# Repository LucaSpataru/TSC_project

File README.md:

# TSC_project
Pentru acest proiect am avut de implementat PCBul unui ebook reader si asamblarea acestuia in carcasa alaturi de o baterie si display.
Primul pas al proiectului a fost creearea schemei electrice ce consta in plasarea si conectarea componentelor.
Componenta principala este microcontrollerul ESP32-C6 care gestioneaza și coordoneaza functionarea celorlalte componente.
# Pini folositi
| Componentă                            | Pini ESP C6                         | Funcție                                                       |
|--------------------------------------|-------------------------------------|---------------------------------------------------------------|
| SAMACSYS_PARTS_USB4110-GF-AUSB4      | 13 (USB_D-), 14 (USB_D+)            | Încărcare baterie via USB                                     |
| QWIIC_RIGHT_ANGLE + BME680           | 19 (SDA), 20 (SCL)                  | Măsurare temperatură, calitate aer, umiditate (energy mgmt)  |
| 112A-TAAR-R03_ATTEND (SD card port)  | 4 (SS_SD), 6 (SCK), 7 (MOSI), 27 (MISO) | Transfer de date (card SD)                                 |
| FH34SRJ-24S-0.5SH_99_ (Display header)| 7 (MOSI), 6 (SCK), 11 (EPD_CS), 5 (EPD_DC), 21 (EPD_RST), 26 (EPD_BUSY) | Conectare display          |
| W25Q512JVEIQ (64MB Flash extern)     | 6 (SCK), 7 (MOSI), 27 (MISO), 12 (FLASH_CS) | Stocare de date                                       |
| Butoane (CHANGE, RESET, BOOT)        | 23 (IO/CHANGE), 3 (RESET), 15 (IO/BOOT) | Interfață utilizator (comenzi)                          |
| DS3231SN# (RTC module)               | 8 (INT_RTC), 19 (SDA), 20 (SCL), 9 (32KHZ), 16 (RTC_RST) | Ceas în timp real                              |

De asemenea sunt implementate test paduri, un regulator de tensiune si linii de protectie pentru a putea asigura functionarea corecta a dispozitivului.

Urmatoarul pas a constat in aranjarea componentelor pe placa, decuparea acesteia pentru a se potrivi in carcasa si pentru a nu incurca alte componente precum microcontrollerul si butoanele,
rutarea semnalelor si desenarea planului de masa pe fata si pe spate.
Am intampinat unele probleme precum marimea padurilor pentru componenta MAX17048G+T10 care nu se potriveau cu regulile de rutare, si marimea padurilor bobinei care erau prea mici - am modificat footprintul componentelor.
Am dat approve la 2 erori comune de tip Board Outline Clearance pentru mufa USB4.
Am plasat componentele cat mai eficient, si de asemenea am aranjat ca numele componentelor sa fie vizibile pe silkscreen.

Mai departe am cautat pentru fiecare componenta folosita modele 3D unde am comparat footprinturile pieselor gasite pentru a alege modelul corespunzator.

Ultimul pas a constat in partea 3D unde am plasat placa in carcasa, aici am facut o modificare ce se poate observa in imaginile buttons_mod, deoarece felul in care am pus butoanele se intersectau cu o bucata de plastic
care am micsorat-o. Butoanele ar trebuii sa functioneze fara probleme acum.
Dupa ce m-am asigurat ca mufele sunt aliniate cu componentele ce ies de pe placa, am creeat un model de baterie si unul de display si le-am aranjat si pe acestea in interiorul dispozitivului.

In cele din urma am generat fisierele BOM, PNP si gerbers care se afla in fisierul Manufacturing.
De asemenea am realizat o animatie cu exploded view, dar si un fisier .step cum este specificat in cerinta.
# BOM
| Componentă                     | Link de cumpărare |
|----------------------------|-------------------|
| ADAFRUIT_LEDCHIP-LED0603   | [Mouser](https://ro.mouser.com/ProductDetail/ams-OSRAM/KW-EELP41.RU-S1U1-3K6L-3X4X-5-R18?qs=sGAEpiMZZMt82OzCyDsLFIOEctO0UgBCyNaG5LP3KGg%3D)                 |
| SJ                         | [Mouser](https://ro.mouser.com/ProductDetail/Chip-Quik/WWSWLT.040-200g?qs=i8QVZAFTkqRTFq30mTreAQ%3D%3D)                 |
| CPH3225A (Supercapacitor)  | [Mouser](https://ro.mouser.com/ProductDetail/Seiko-Semiconductors/CPH3225A?qs=3etwrb1wR%252BhUOph6lAO7eg%3D%3D) |
| DS3231SN# (RTC)           | [SnapEDA](https://www.snapeda.com/parts/DS3231SN%23/Analog+Devices/view-part/?ref=eda) |
| ESP32-C6-WROOM-1-N8       | [SnapEDA](https://www.snapeda.com/parts/ESP32-C6-WROOM-1-N8/Espressif+Systems/view-part/?ref=eda) |
| FH34SRJ-24S-0.5SH_99_     | [Mouser](https://www.mouser.co.uk/ProductDetail/Hirose-Connector/FH34SRJ-24S-0.5SH99?qs=vcbW%252B4%252BSTIpKBl5ap9J8Fw%3D%3D) |
| MAX17048G+T10 (Fuel Gauge)| [SnapEDA](https://www.snapeda.com/parts/MAX17048G+T10/Analog+Devices/view-part/?ref=eda) |
| MBR0530 (Schottky Diode)  | [SnapEDA](https://www.snapeda.com/parts/MBR0530/Onsemi/view-part/?ref=eda) |
| PGB1010603MR (TVS Diode)  | [SnapEDA](https://www.snapeda.com/parts/PGB1010603MR/Littelfuse/view-part/?ref=eda) |
| SI1308EDL-T1-GE3 (MOSFET) | [SnapEDA](https://www.snapeda.com/parts/SI1308EDL-T1-GE3/Vishay+Siliconix/view-part/?ref=eda) |
| USBLC6-2SC6Y (ESD Protection)| [SnapEDA](https://www.snapeda.com/parts/USBLC6-2SC6Y/STMicroelectronics/view-part/?ref=eda) |
| W25Q512JVEIQ (Flash Memory)| [SnapEDA](https://www.snapeda.com/parts/W25Q512JVEIQ/Winbond+Electronics/view-part/?ref=eda) |
| XC6220A331MR-G (LDO Regulator)| [Mouser](https://www.mouser.co.uk/ProductDetail/Torex-Semiconductor/XC6220A331MR-G?qs=AsjdqWjXhJ8ZSWznL1J0gg%3D%3D) |
| BD5229G-TR (Voltage Detector)| [Mouser](https://www.mouser.co.uk/ProductDetail/ROHM-Semiconductor/BD5229G-TR?qs=4kLU8WoGk0vvnhrrYwdszw%3D%3D) |
| BME680 (Environmental Sensor)| [Mouser](https://ro.mouser.com/ProductDetail/Bosch-Sensortec/BME680?qs=v271MhAjFHjo0yA%2FC4OnDQ%3D%3D)                 |
| 112A-TAAR-R03_ATTEND (SD Card Socket)| [DigiKey](https://www.digikey.ro/en/products/detail/attend-technology/112A-TAAR-R03/17633923)                 |

# Diagrama

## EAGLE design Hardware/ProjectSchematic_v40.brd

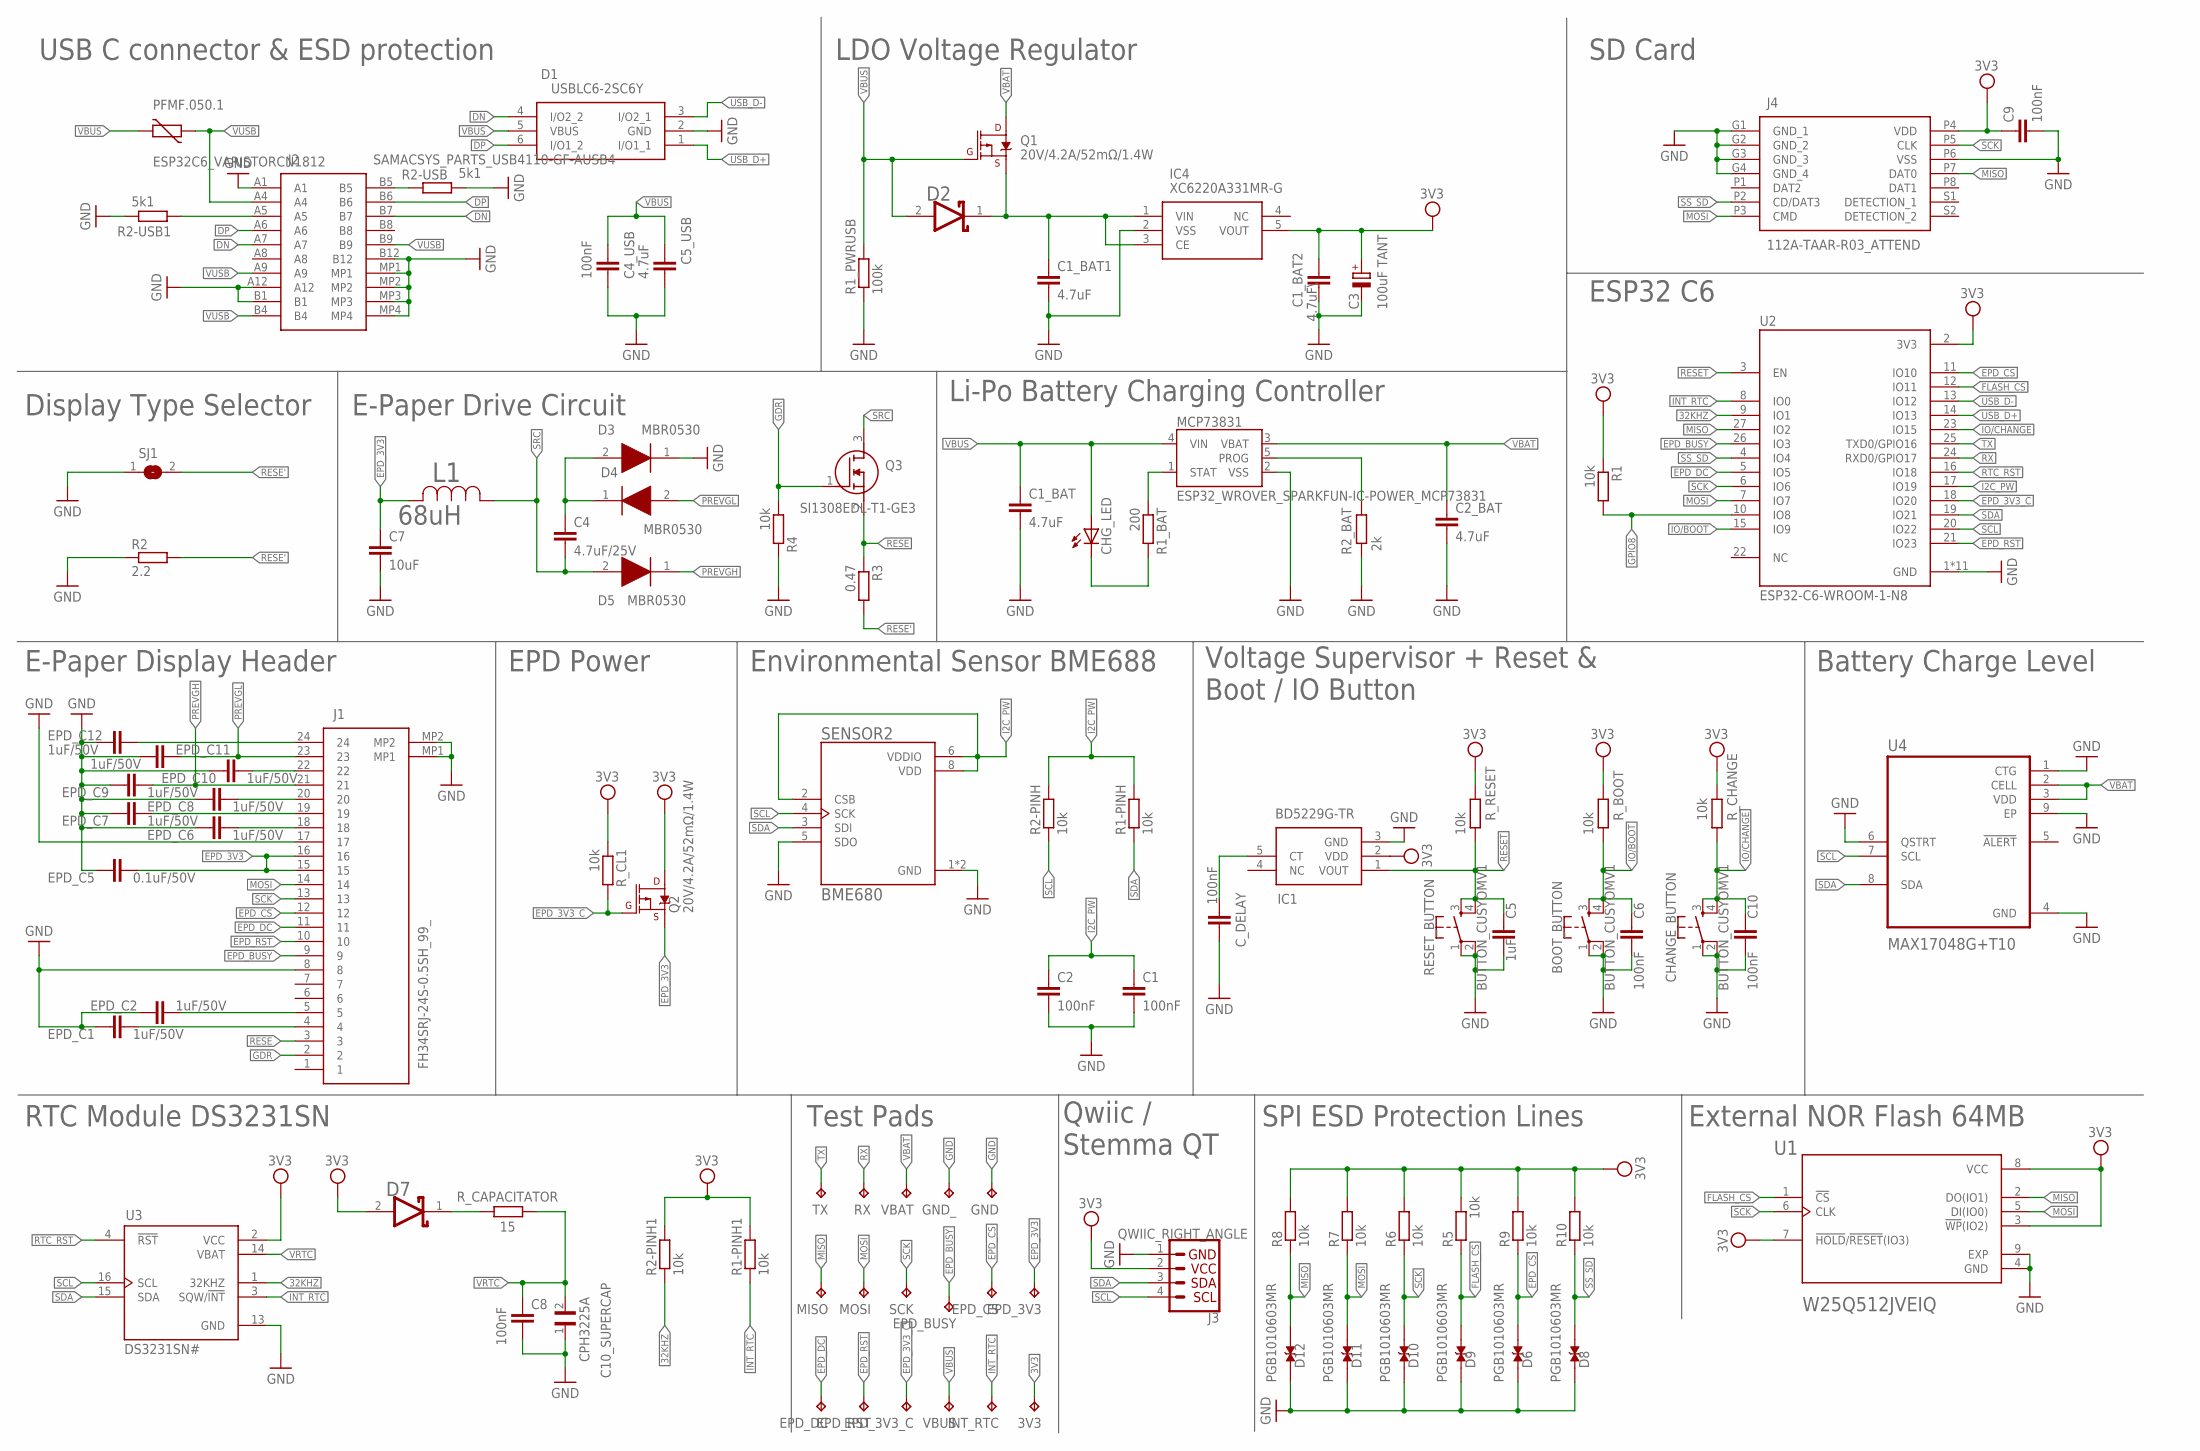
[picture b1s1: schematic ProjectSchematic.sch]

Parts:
3V3: TPTP20R; TP20R
BOOT_BUTTON: BUTTON_CUSYOMV1; MYBUTTON
C1, C2, C4_USB, C6, C8, C9, C10: 100nF; ESP32_WROVER_EAGLE-LTSPICE_C0402
C1_BAT, C1_BAT1, C2_BAT, C5_USB: 4.7uF; ESP32_WROVER_EAGLE-LTSPICE_C0402
C1_BAT2: 4.7uF\; ESP32_WROVER_EAGLE-LTSPICE_C0402
C3: 100uF TANT; RCL_CT3528
C4: 4.7uF/25V; ESP32_WROVER_EAGLE-LTSPICE_C0402
C5: 1uF; ESP32_WROVER_EAGLE-LTSPICE_C0402
C7: 10uF; ESP32_WROVER_EAGLE-LTSPICE_C0402
C10_SUPERCAP: CPH3225A; CAPCP3225X100N
CHANGE_BUTTON: BUTTON_CUSYOMV1; MYBUTTON
CHG_LED: ADAFRUIT_LEDCHIP-LED0603; ADAFRUIT_CHIP-LED0603
C_DELAY: 100nF; ESP32_WROVER_EAGLE-LTSPICE_C0402
D1: USBLC6-2SC6Y; SOT95P280X145-6N
D2, D7: ESP32_WROVER_AVX---SD0805S020S1R0_AVX_SD0805S020S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; ESP32_WROVER_AVX---SD0805S020S1R0_AVX_SD0805S020S1R0_0
D3, D4, D5: MBR0530; SOD3716X135N
D6, D8, D9, D10, D11, D12: PGB1010603MR; DIOC1608X36N
EPD_3V3, EPD_3V3_C: TPTP20R; TP20R
EPD_BUSY: TPTP20R; TP20R
EPD_C1, EPD_C2, EPD_C6, EPD_C7, EPD_C8, EPD_C9, EPD_C10, EPD_C11, EPD_C12: 1uF/50V; ESP32_WROVER_EAGLE-LTSPICE_C0402
EPD_C5: 0.1uF/50V; ESP32_WROVER_EAGLE-LTSPICE_C0402
EPD_CS: TPTP20R; TP20R
EPD_DC: TPTP20R; TP20R
EPD_RST: TPTP20R; TP20R
GND: TPTP20R; TP20R
GND_: TPTP20R; TP20R
IC1: BD5229G-TR; SOT95P280X125-5N
IC4: XC6220A331MR-G; SOT95P280X120-5N
INT_RTC: TPTP20R; TP20R
J1: FH34SRJ-24S-0.5SH_99_; FH34SRJ24S05SH99
J2: SAMACSYS_PARTS_USB4110-GF-AUSB4; SAMACSYS_PARTS_USB4110GFA
J3: QWIIC_RIGHT_ANGLE; JST04_1MM_RA
J4: 112A-TAAR-R03_ATTEND; 112ATAARR03ATTEND
L1: 68uH; IND_4828-WE-TPC_WRE
MCP73831: ESP32_WROVER_SPARKFUN-IC-POWER_MCP73831; ESP32_WROVER_SPARKFUN-IC-POWER_SOT23-5
MISO: TPTP20R; TP20R
MOSI: TPTP20R; TP20R
PFMF.050.1: ESP32C6_VARISTORCN1812; ESP32C6_VARISTOR_CT/CN1812
Q1, Q2: 20V/4.2A/52mΩ/1.4W; ESP32_WROVER_SPARKFUN-DISCRETESEMI_SOT23-3
Q3: SI1308EDL-T1-GE3; SOT65P210X110-3N
R1, R1-PINH, R1-PINH1, R2-PINH, R2-PINH1, R4, R5, R6, R7, R8, R9, R10: 10k; ESP32_WROVER_EAGLE-LTSPICE_R0402
R1_BAT: 200; ESP32_WROVER_EAGLE-LTSPICE_R0402
R1_PWRUSB: 100k; ESP32_WROVER_EAGLE-LTSPICE_R0402
R2: 2.2; ESP32_WROVER_EAGLE-LTSPICE_R0402
R2-USB, R2-USB1: 5k1; ESP32_WROVER_EAGLE-LTSPICE_R0402
R2_BAT: 2k; ESP32_WROVER_EAGLE-LTSPICE_R0402
R3: 0.47; ESP32_WROVER_EAGLE-LTSPICE_R0402
RESET_BUTTON: BUTTON_CUSYOMV1; MYBUTTON
RX: TPTP20R; TP20R
R_BOOT: 10k; ESP32_WROVER_EAGLE-LTSPICE_R0402
R_CAPACITATOR: 15; ESP32_WROVER_EAGLE-LTSPICE_R0402
R_CHANGE: 10k; ESP32_WROVER_EAGLE-LTSPICE_R0402
R_CL1: 10k; ESP32_WROVER_EAGLE-LTSPICE_R0402
R_RESET: 10k; ESP32_WROVER_EAGLE-LTSPICE_R0402
SCK: TPTP20R; TP20R
SENSOR2: BME680; ESP32_WROVER_BME680_PSON80P300X300X100-8N
SJ1: SJ
TX: TPTP20R; TP20R
U1: W25Q512JVEIQ; SON127P600X800X80-9N
U2: ESP32-C6-WROOM-1-N8; XCVR_ESP32-C6-WROOM-1-N8
U3: DS3231SN#; SOIC127P1032X265-16N
U4: MAX17048G+T10; SON50P200X200X80-9N
VBAT: TPTP20R; TP20R
VBUS: TPTP20R; TP20R

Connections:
3V3: 3V3.TP, C1_BAT2.1, C3.+, C9.1, D7.2 (ANODE), IC1.2 (VDD), IC4.5 (VOUT), J3.2, J4.P4 (VDD), Q2.3 (D), R1.1, R1-PINH1.2, R2-PINH1.2, R5.2, R6.2, R7.2, R8.2, R9.2, R10.2, R_BOOT.2, R_CHANGE.2, R_CL1.1, R_RESET.2, U1.3 (!WP!(IO2)), U1.7 (!HOLD!/!RESET!(IO3)), U1.8 (VCC), U2.2 (3V3), U3.2 (VCC)
32KHZ: R2-PINH1.1, U2.9 (IO1), U3.1 (32KHZ)
DN: D1.4 (I/O2_2), J2.A7, J2.B7
DP: D1.6 (I/O1_2), J2.A6, J2.B6
EPD_3V3: C7.1, EPD_3V3.TP, EPD_C5.1, J1.15, J1.16, L1.2, Q2.2 (S)
EPD_3V3_C: EPD_3V3_C.TP, Q2.1 (G), R_CL1.2, U2.18 (IO20)
EPD_BUSY: EPD_BUSY.TP, J1.9, U2.26 (IO3)
EPD_CS: D6.2, EPD_CS.TP, J1.12, R9.1, U2.11 (IO10)
EPD_DC: EPD_DC.TP, J1.11, U2.5 (IO5)
EPD_RST: EPD_RST.TP, J1.10, U2.21 (IO23)
FLASH_CS: D9.2, R5.1, U1.1 (!CS), U2.12 (IO11)
GDR: J1.2, Q3.1 (G), R4.1
GND: BOOT_BUTTON.1, BOOT_BUTTON.2, C1.2, C1_BAT.2, C1_BAT1.2, C1_BAT2.2, C2.2, C2_BAT.2, C3.-, C4_USB.2, C5.2, C5_USB.2, C6.2, C7.2, C8.2, C9.2, C10.2, C10_SUPERCAP.1, CHANGE_BUTTON.1, CHANGE_BUTTON.2, C_DELAY.2, D1.2 (GND), D3.1 (K), D6.1, D8.1, D9.1, D10.1, D11.1, D12.1, EPD_C1.2, EPD_C2.2, EPD_C5.2, EPD_C6.2, EPD_C7.2, EPD_C8.2, EPD_C9.2, EPD_C10.2, EPD_C11.2, EPD_C12.2, GND.TP, GND_.TP, IC1.3 (GND), IC4.2 (VSS), J1.8, J1.17, J1.MP1, J1.MP2, J2.A1, J2.A12, J2.B1, J2.B12, J2.MP1, J2.MP2, J2.MP3, J2.MP4, J3.1, J4.G1 (GND_1), J4.G2 (GND_2), J4.G3 (GND_3), J4.G4 (GND_4), J4.P6 (VSS), MCP73831.2 (VSS), R1_PWRUSB.1, R2.1, R2-USB.2, R2-USB1.1, R2_BAT.2, R4.2, RESET_BUTTON.1, RESET_BUTTON.2, SENSOR2.1 (GND), SENSOR2.5 (SDO), SENSOR2.7 (GND), SJ1.1, U1.4 (GND), U1.9 (EXP), U2.1 (GND), U2.28 (GND), U2.29_1 (GND), U2.29_2 (GND), U2.29_3 (GND), U2.29_4 (GND), U2.29_5 (GND), U2.29_6 (GND), U2.29_7 (GND), U2.29_8 (GND), U2.29_9 (GND), U3.13 (GND), U4.1 (CTG), U4.4 (GND), U4.6 (QSTRT), U4.9 (EP)
GPIO8: R1.2, U2.10 (IO8)
I2C_PW: C1.1, C2.1, R1-PINH.2, R2-PINH.2, SENSOR2.2 (CSB), SENSOR2.6 (VDDIO), SENSOR2.8 (VDD), U2.17 (IO19)
INT_RTC: INT_RTC.TP, R1-PINH1.1, U2.8 (IO0), U3.3 (SQW/!INT)
IO/BOOT: BOOT_BUTTON.3, BOOT_BUTTON.4, C6.1, R_BOOT.1, U2.15 (IO9)
IO/CHANGE: C10.1, CHANGE_BUTTON.3, CHANGE_BUTTON.4, R_CHANGE.1, U2.23 (IO15)
MISO: D12.2, J4.P7 (DAT0), MISO.TP, R8.1, U1.2 (DO(IO1)), U2.27 (IO2)
MOSI: D11.2, J1.14, J4.P3 (CMD), MOSI.TP, R7.1, U1.5 (DI(IO0)), U2.7 (IO7)
unnamed: J2.B5, R2-USB.1
unnamed: J2.A5, R2-USB1.2
unnamed: C_DELAY.1, IC1.5 (CT)
unnamed: MCP73831.1 (STAT), R1_BAT.1
unnamed: C1_BAT1.1, D2.1 (CATHODE), IC4.1 (VIN), IC4.3 (CE), Q1.2 (S)
unnamed: CHG_LED.C, R1_BAT.2
unnamed: C4.1, D3.2 (A), D4.1 (K)
unnamed: MCP73831.5 (PROG), R2_BAT.1
unnamed: EPD_C2.1, J1.5
unnamed: EPD_C1.1, J1.4
unnamed: D7.1 (CATHODE), R_CAPACITATOR.2
unnamed: EPD_C12.1, J1.24
unnamed: EPD_C10.1, J1.22
unnamed: EPD_C7.1, J1.19
unnamed: EPD_C8.1, J1.20
unnamed: EPD_C6.1, J1.18
PREVGH: D5.1 (K), EPD_C9.1, J1.21
PREVGL: D4.2 (A), EPD_C11.1, J1.23
RESE: J1.3, Q3.2 (S), R3.1
RESE': R2.2, R3.2, SJ1.2
RESET: C5.1, IC1.1 (VOUT), RESET_BUTTON.3, RESET_BUTTON.4, R_RESET.1, U2.3 (EN)
RTC_RST: U2.16 (IO18), U3.4 (!RST)
RX: RX.TP, U2.24 (RXD0/GPIO17)
SCK: D10.2, J1.13, J4.P5 (CLK), R6.1, SCK.TP, U1.6 (CLK), U2.6 (IO6)
SCL: J3.4, R2-PINH.1, SENSOR2.4 (SCK), U2.20 (IO22), U3.16 (SCL), U4.7 (SCL)
SDA: J3.3, R1-PINH.1, SENSOR2.3 (SDI), U2.19 (IO21), U3.15 (SDA), U4.8 (SDA)
SRC: C4.2, D5.2 (A), L1.1, Q3.3 (D)
SS_SD: D8.2, J4.P2 (CD/DAT3), R10.1, U2.4 (IO4)
TX: TX.TP, U2.25 (TXD0/GPIO16)
USB_D+: D1.1 (I/O1_1), U2.14 (IO13)
USB_D-: D1.3 (I/O2_1), U2.13 (IO12)
VBAT: C2_BAT.1, MCP73831.3 (VBAT), Q1.3 (D), U4.2 (CELL), U4.3 (VDD), VBAT.TP
VBUS: C1_BAT.1, C4_USB.1, C5_USB.1, CHG_LED.A, D1.5 (VBUS), D2.2 (ANODE), MCP73831.4 (VIN), PFMF.050.1.2, Q1.1 (G), R1_PWRUSB.2, VBUS.TP
VRTC: C8.1, C10_SUPERCAP.2, R_CAPACITATOR.1, U3.14 (VBAT)
VUSB: J2.A4, J2.A9, J2.B4, J2.B9, PFMF.050.1.1

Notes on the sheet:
USB C connector & ESD protection
LDO Voltage Regulator
SD Card
Display Type Selector
E-Paper Drive Circuit
Li-Po Battery Charging Controller
ESP32 C6
E-Paper Display Header
EPD Power
Environmental Sensor BME688
Voltage Supervisor + Reset & Boot / IO Button
Battery Charge Level
RTC Module DS3231SN
Test Pads
Qwiic / Stemma QT
SPI ESD Protection Lines
External NOR Flash 64MB

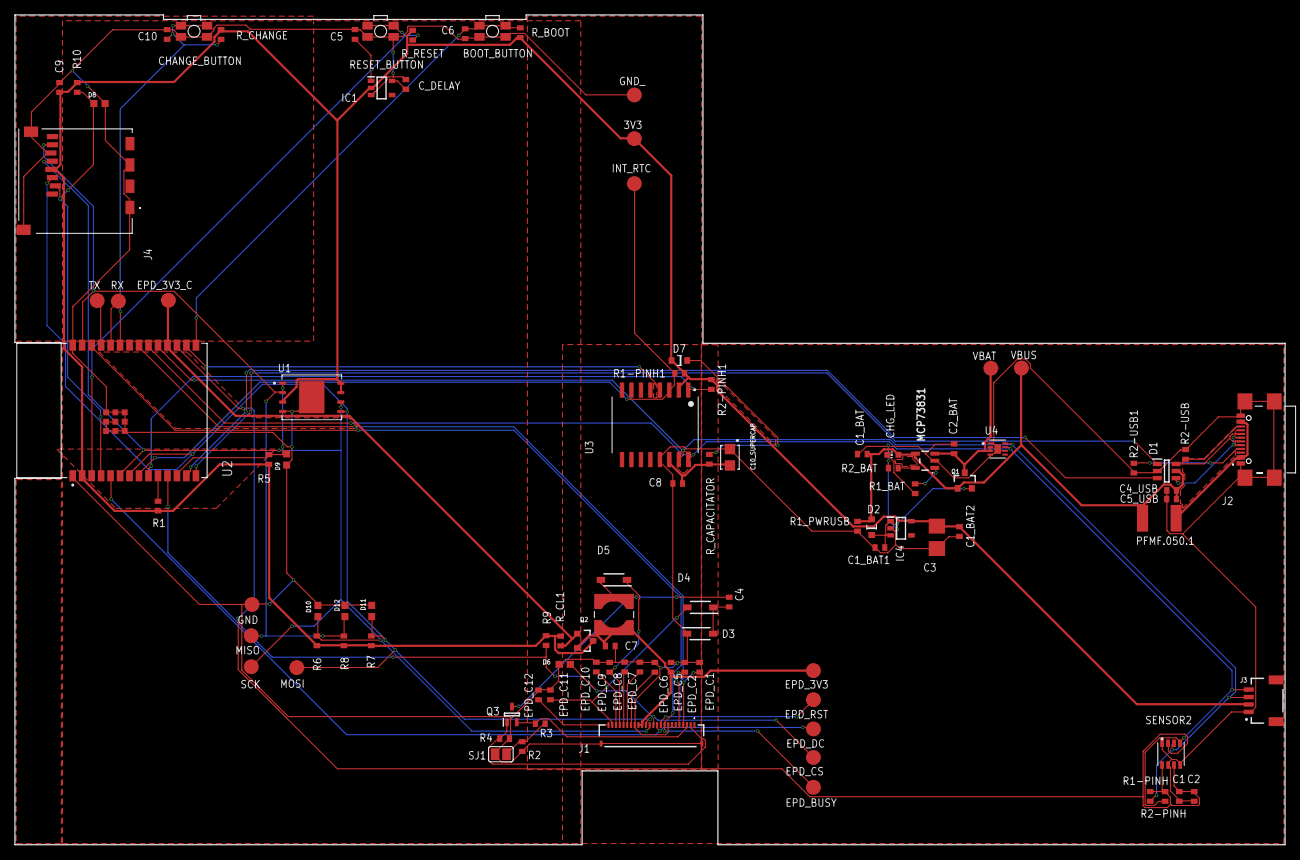
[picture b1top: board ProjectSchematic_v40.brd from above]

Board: 2 copper layers, 170.2 x 111.2 mm, 103 parts (0 on the bottom side), 55 nets.

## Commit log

2025-04-06 Created LICENSE
2025-04-11 Am modificat valorile de pe silk screen
2025-04-11 Am sters fisiere adaugate din greseala
2025-04-11 Create ProjectSchematic_v40.brd
    Am rearanjat numele pe silk screen si am sters valorile
2025-04-14 Am sters designul vechi
2025-04-14 Am adaugat designul modificat
2025-04-14 Am adaugat fisierul .step cu noul design
2025-04-14 Update README.md
    Am adaugat tabel BOM si am realizat modificari estetice

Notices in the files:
parts and their libraries:
ProjectLibrary: COPYRIGHT: Copyright (C) 2024 Ultra Librarian. All rights reserved.
